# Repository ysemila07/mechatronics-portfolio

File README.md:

# Mechatronics Engineering Portfolio

Project portfolio from a Mechatronics Engineering degree (First Class Honours, University of
Wollongong), covering control systems, mechanical design, industrial automation, and an engineering
internship. My most visual/flagship projects — the autonomous radar robot, the race car PCB, and the
AVR embedded work — have their own dedicated repos, linked below.

**Contact:** add your email / LinkedIn / phone here.

## Featured projects (own repos)

| Project | Area |
|---|---|
| [Autonomous Omni-Wheel Robot — mmWave Radar Navigation](https://github.com/ysemila07/mmwave-radar-robot) | Honours thesis · robotics, sensing, path planning |
| [Race Car Steering Wheel Display — UOW Motorsport](https://github.com/ysemila07/racecar-steering-wheel-display) | Embedded/PCB · STM32, KiCad, CAN bus |
| [AVR Embedded Systems](https://github.com/ysemila07/avr-embedded-systems) | Embedded C · ATmega16 register-level programming |

## Other projects (this repo)

| # | Project | Area |
|---|---------|------|
| 1 | [Robotic Manipulator — Kinematic & Singularity Analysis](01-robotic-manipulator/) | Robotics · kinematics, MATLAB/ARTE |
| 2 | [Industrial Automation & PLC Control](02-plc-industrial-automation/) | PLC · Siemens TIA Portal, Simulink/Simscape |
| 3 | [Fuzzy Logic & ANFIS Control](03-fuzzy-anfis-control/) | Intelligent control · MATLAB/Simulink |
| 4 | [Hobbyist Lathe](04-hobbyist-lathe/) | Mechanical design · Inventor CAD |
| 5 | [Engineering Internship — Intermarc Global](05-internship-summary/) | Building services · compliance auditing, BMS |

## Skills demonstrated across these projects

- **Embedded/firmware:** C (ATmega16 bare-metal), STM32, register-level peripheral configuration
  (GPIO, USART, Timers/PWM, ADC, interrupts)
- **Robotics & control:** path planning (A*), kinematics/Jacobian analysis, PID/fuzzy/ANFIS control
  design and tuning (Ziegler-Nichols), sensor fusion (mmWave radar, ultrasonic)
- **Industrial automation:** Siemens TIA Portal ladder logic, analogue I/O scaling/calibration,
  PLC-based control of motors, sensors, and safety interlocks
- **Simulation/modelling:** MATLAB, Simulink, Simscape, MATLAB Fuzzy Logic Toolbox, ARTE Robotics
  Toolbox
- **Mechanical design:** Autodesk Inventor, drivetrain/gearbox sizing, power/torque budgeting, FEA
- **PCB/electronics:** KiCad schematic and PCB layout, CAN bus integration
- **Building services:** compliance auditing against AS/NZS standards and the NCC, Building
  Management Systems (BACnet, Modbus, KNX, DALI)

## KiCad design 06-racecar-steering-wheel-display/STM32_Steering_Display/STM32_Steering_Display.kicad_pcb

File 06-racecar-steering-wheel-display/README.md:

# Race Car Steering Wheel Display — UOW Motorsport (Team XPEDE)

**Course:** ECTE351 (Engineering Design and Management 3) | **Team:** XPEDE (5 members)

A custom STM32-based steering wheel display and driver control system built for UOW Motorsport's
electric formula-style vehicle. Four push buttons on the wheel let the driver adjust
torque-vectoring and traction-control settings from the cockpit; the selected values are sent over
the vehicle's CAN bus and shown on the display.

**Role on the team:** Finance & Procurement Lead. Contributed to the project's reports and
presentations, the ethics and management assessments, the innovation-fair poster, video demo
production, and stayed engaged with the hardware/software design to support the team where needed.

## Hardware

Custom PCB (`STM32_Steering_Display/`, KiCad project) fabricated via JLCPCB; components sourced from
JLCPCB, Mouser, RS, and the university's SECTE store.
- `STM32_Steering_Display.kicad_sch` / `.kicad_pcb` — main board schematic and layout
- `IO_switches.kicad_sch` — button/IO switch schematic

## Visual assets

`Steering Wheel Display & Driver Control System - XPEDE.mp4` — demo video of the working display
(transcript included alongside it in the original folder), and `XPEDE Trade Fair Vid.mp4` — trade
fair footage likely showing the board mounted in the car. Both too large for this repo; worth
uploading to YouTube/Drive and linking. `XPEDE A1 Poster.pdf` can be repurposed as a static graphic.

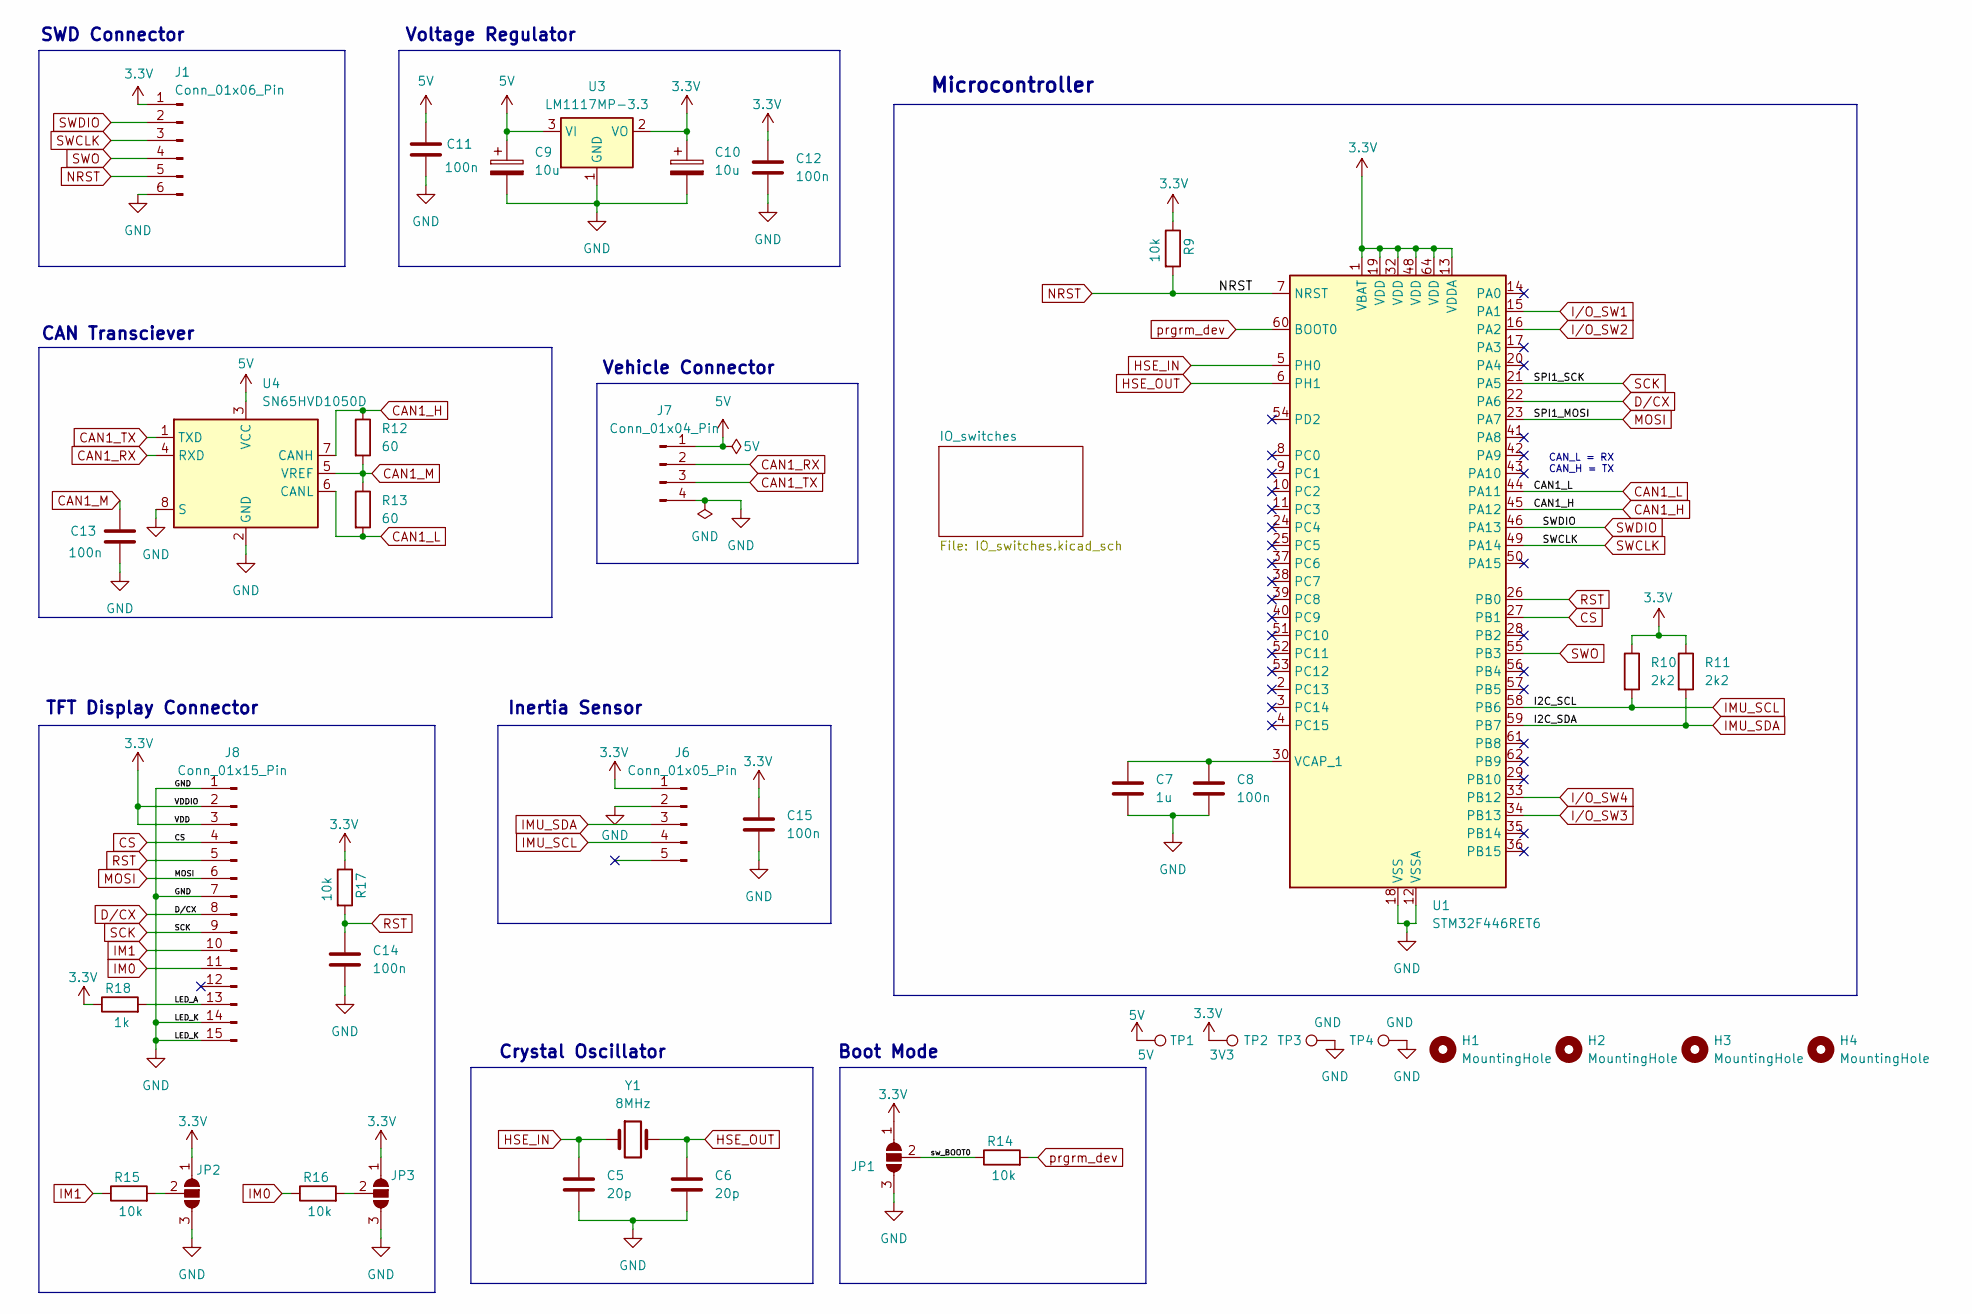
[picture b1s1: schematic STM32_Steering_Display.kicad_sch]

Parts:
C5, C6: 20p; C_0805_2012Metric_Pad1.18x1.45mm_HandSolder
C7: 1u; C_0805_2012Metric_Pad1.18x1.45mm_HandSolder
C8, C11, C12, C13, C14, C15: 100n; C_0805_2012Metric_Pad1.18x1.45mm_HandSolder
C9, C10: 10u; CP_EIA-2012-15_AVX-P_Pad1.30x1.05mm_HandSolder
H1, H2, H3, H4: MountingHole; MountingHole_3.2mm_M3
J1: Conn_01x06_Pin; PinHeader_1x06_P2.54mm_Vertical
J6: Conn_01x05_Pin; PinHeader_1x05_P2.54mm_Vertical
J7: Conn_01x04_Pin; JST_EH_S4B-EH_1x04_P2.50mm_Horizontal
J8: Conn_01x15_Pin; Hirose_FH12-15S-0.5SH_1x15-1MP_P0.50mm_Horizontal
JP1, JP2, JP3: SolderJumper_3_Open; SolderJumper-3_P1.3mm_Open_RoundedPad1.0x1.5mm_NumberLabels
R9, R14, R15, R16, R17: 10k; R_0805_2012Metric_Pad1.20x1.40mm_HandSolder
R10, R11: 2k2; R_0805_2012Metric_Pad1.20x1.40mm_HandSolder
R12, R13: 60; R_0805_2012Metric_Pad1.20x1.40mm_HandSolder
R18: 1k; R_0805_2012Metric_Pad1.20x1.40mm_HandSolder
TP1: 5V; TestPoint_Pad_1.5x1.5mm
TP2: 3V3; TestPoint_Pad_1.5x1.5mm
TP3, TP4: GND; TestPoint_Pad_1.5x1.5mm
U1: STM32F446RET6; LQFP-64_10x10mm_P0.5mm
U3: LM1117MP-3.3; SOT-223-3_TabPin2
U4: SN65HVD1050D; SOIC-8_3.9x4.9mm_P1.27mm
Y1: 8MHz; Crystal_HC49-4H_Vertical

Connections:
3.3V: C10.1, C12.1, C15.1, J1.1, J6.1, J8.2, J8.3, JP1.1 (A), JP2.1 (A), JP3.1 (A), R9.1, R10.1, R11.1, R17.1, R18.1, TP2.1, U1.1 (VBAT), U1.13 (VDDA), U1.19 (VDD), U1.32 (VDD), U1.48 (VDD), U1.64 (VDD), U3.2 (VO); also elsewhere on the board
5V: C9.1, C11.1, J7.1, TP1.1, U3.3 (VI), U4.3 (VCC)
/LED_A: J8.13, R18.2
/sw_BOOT0: JP1.2 (C), R14.1
CAN1_H: R12.1, U1.45 (PA12), U4.7 (CANH)
CAN1_L: R13.2, U1.44 (PA11), U4.6 (CANL)
CAN1_M: C13.1, R12.2, R13.1, U4.5 (VREF)
CAN1_RX: J7.2, U4.4 (RXD)
CAN1_TX: J7.3, U4.1 (TXD)
CS: J8.4, U1.27 (PB1)
D/CX: J8.8, U1.22 (PA6)
GND: C5.2, C6.2, C7.2, C8.2, C9.2, C10.2, C11.2, C12.2, C13.2, C14.2, C15.2, J1.6, J6.2, J7.4, J8.1, J8.7, J8.14, J8.15, JP1.3 (B), JP2.3 (B), JP3.3 (B), TP3.1, TP4.1, U1.12 (VSSA), U1.18 (VSS), U1.31 (VSS), U1.47 (VSS), U1.63 (VSS), U3.1 (GND), U4.2 (GND), U4.8 (S); also elsewhere on the board
HSE_IN: C5.1, U1.5 (PH0), Y1.1
HSE_OUT: C6.1, U1.6 (PH1), Y1.2
IM0: J8.11, R16.1
IM1: J8.10, R15.1
IMU_SCL: J6.4, R10.2, U1.58 (PB6)
IMU_SDA: J6.3, R11.2, U1.59 (PB7)
I/O_SW1: U1.15 (PA1); also elsewhere on the board
I/O_SW2: U1.16 (PA2); also elsewhere on the board
I/O_SW3: U1.34 (PB13); also elsewhere on the board
I/O_SW4: U1.33 (PB12); also elsewhere on the board
MOSI: J8.6, U1.23 (PA7)
NRST: J1.5, R9.2, U1.7 (NRST)
unnamed: JP2.2 (C), R15.2
unnamed: JP3.2 (C), R16.2
unnamed: C7.1, C8.1, U1.30 (VCAP_1)
RST: C14.1, J8.5, R17.2, U1.26 (PB0)
SCK: J8.9, U1.21 (PA5)
SWCLK: J1.3, U1.49 (PA14)
SWDIO: J1.2, U1.46 (PA13)
SWO: J1.4, U1.55 (PB3)
prgrm_dev: R14.2, U1.60 (BOOT0)

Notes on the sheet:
CAN Transciever
TFT Display Connector
SWD Connector
Boot Mode
CAN_L = RX CAN_H = TX
Microcontroller
Inertia Sensor
Vehicle Connector
Crystal Oscillator
Voltage Regulator

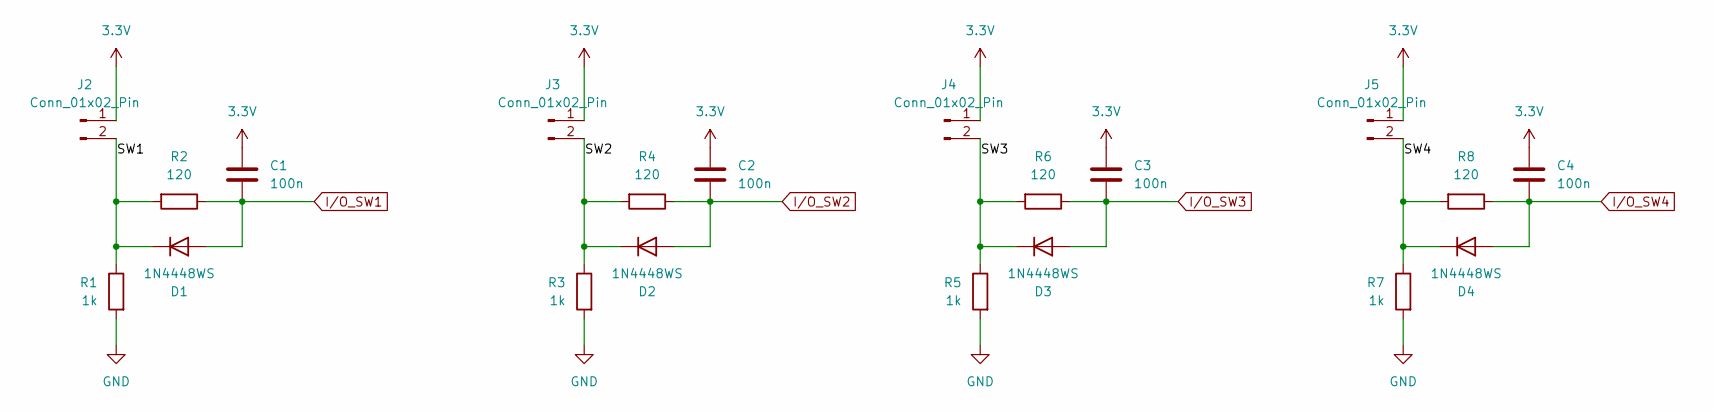
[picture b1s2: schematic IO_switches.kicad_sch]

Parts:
C1, C2, C3, C4: 100n; C_0805_2012Metric_Pad1.18x1.45mm_HandSolder
D1, D2, D3, D4: 1N4448WS; D_SOD-323
J2, J3, J4, J5: Conn_01x02_Pin; JST_EH_S2B-EH_1x02_P2.50mm_Horizontal
R1, R3, R5, R7: 1k; R_0805_2012Metric_Pad1.20x1.40mm_HandSolder
R2, R4, R6, R8: 120; R_0805_2012Metric_Pad1.20x1.40mm_HandSolder

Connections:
3.3V: C1.1, C2.1, C3.1, C4.1, J2.1, J3.1, J4.1, J5.1; also elsewhere on the board
/IO_switches/SW1: D1.1 (K), J2.2, R1.1, R2.2
/IO_switches/SW2: D2.1 (K), J3.2, R3.1, R4.2
/IO_switches/SW3: D3.1 (K), J4.2, R5.1, R6.2
/IO_switches/SW4: D4.1 (K), J5.2, R7.1, R8.2
GND: R1.2, R3.2, R5.2, R7.2; also elsewhere on the board
I/O_SW1: C1.2, D1.2 (A), R2.1; also elsewhere on the board
I/O_SW2: C2.2, D2.2 (A), R4.1; also elsewhere on the board
I/O_SW3: C3.2, D3.2 (A), R6.1; also elsewhere on the board
I/O_SW4: C4.2, D4.2 (A), R8.1; also elsewhere on the board

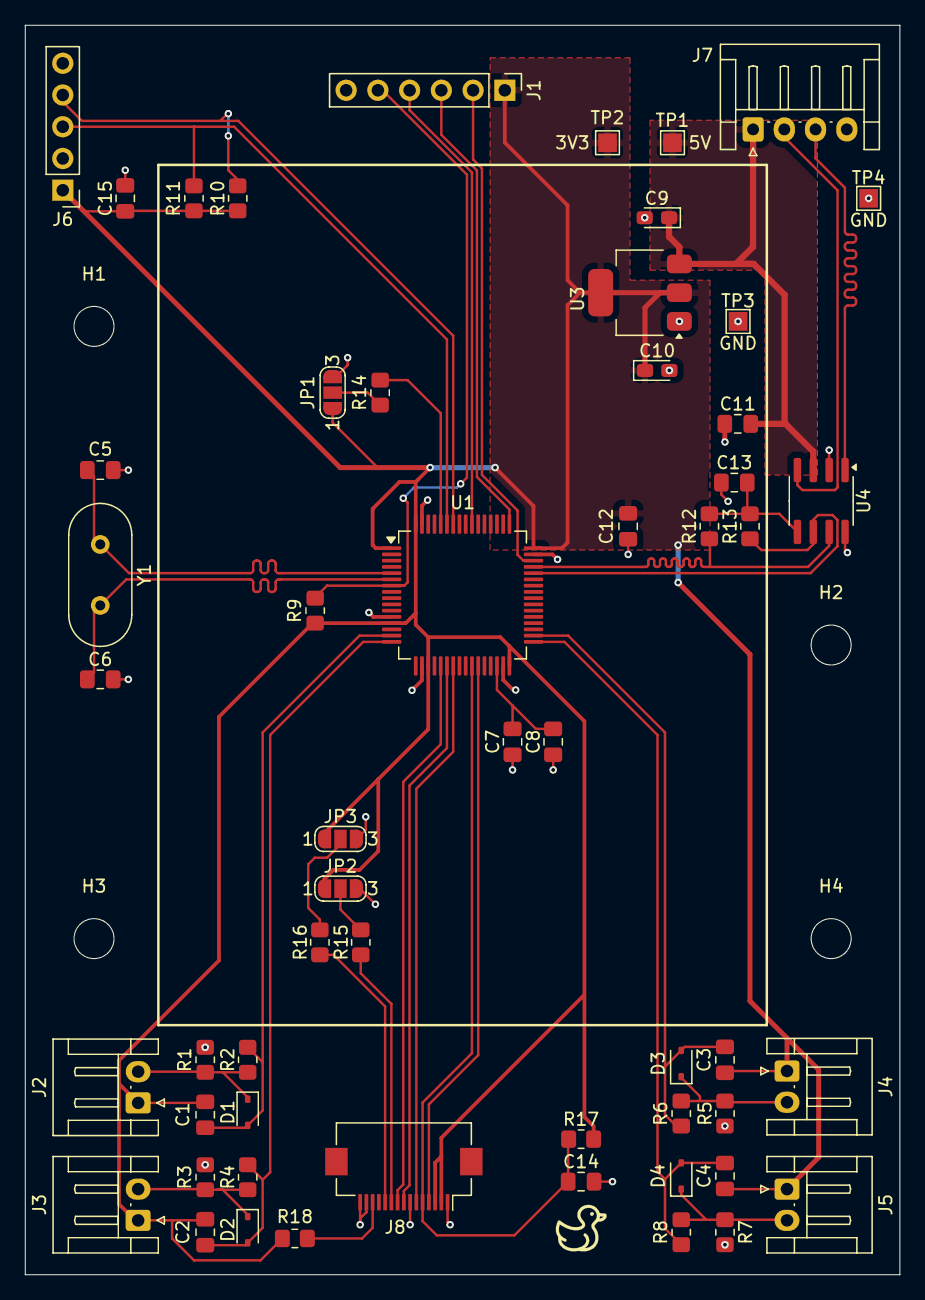
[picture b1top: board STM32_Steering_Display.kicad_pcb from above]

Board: 2 copper layers, 70.0 x 100.0 mm, 60 parts (0 on the bottom side), 37 nets.
